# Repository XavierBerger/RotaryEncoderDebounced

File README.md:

# Rotary Encoder Debounced

A rotary encoder tracks shaft rotation by outputting pulses. However, mechanical switches in encoders suffer from contact bounce, causing false signals.

This projet propose a solution to debounced Rotary Encoder signal at hardware level.

## The Problem

When encoder contacts close or open, they bounce, creating multiple rapid signal changes. These can be misinterpreted as several rotations or direction changes.

*Signal captured on a rotary encoder without debouncer*

*Resulting signal of a noisy input*

## The solutions

### Software Debouncing is not statisfying

Software debouncing filters out noise but has drawbacks:

* Timing needs are precise and hard to maintain at varying speeds.

* Processing overhead increases, burdening limited systems.

* Complexity rises with advanced algorithms.

### Hardware Debouncing is more reliable

This project uses hardware to debounce signals reliably by associating low-pass filters with schmitt triggers.

#### Low-Pass Filter

A simple RC circuit smooths the signal by filtering high-frequency noise, averaging rapid changes.

Filter has been designed to have a cutoff frequency of 1,59kHz with a time constant of 100µs.

#### Schmitt Trigger

Schmitt trigger, with two voltage thresholds, converts the filtered signal to a clean digital output. Hysteresis prevents noise from causing false transitions.

This combination removes bounce issues and provide a clean signal where noise is removed.

Hardware has been designed to use the smallest possible PCB. Pin header have been placed to ensure connectivity as well as mounting solution. Pin header placement have been placed to be compatible with breadboards.

## Realisation
Schematic, PCB, 3D views are designed with KiCad 9 with the following plugins:

* Interactive Html Bom [🔗](https://github.com/openscopeproject/InteractiveHtmlBom)  
  See the bill of material [here](https://xavierberger.github.io/RotaryEncoderDebounced/ibom.html)
* KiCAD JLCPCB tools [🔗](https://github.com/bouni/kicad-jlcpcb-tools)  
  This plugin allows you to search the JLCPCB parts database, assign LCSC article numbers to your parts, generate production files for JLCPCB and much more.
* Fabrication Toolkit [🔗](https://github.com/bennymeg/Fabrication-Toolkit)  
  Toolkit for automating PCB fabrication process with KiCad and JLCPCB. 

*Note: I used* **Fabrication Toolkit** *to generate production file since I noticed that component orientation of component is correct while it wans't in* **KiCAD JLCPCB tools**.

Components have been choosen to be "**Basic**" parts of JLCPCB to reduce the manufactirung cost.

The cost of the PCB fabrication and SMD assembly (so without the rotary encoder and pin headers) is about 7€ for 5 pieces.

## Analysis of results

On the oscilloscope, we can see a clean signal. The noise has been filtered-out.

*Signal captured on a rotary encoder with hardware debouncer*

The resulting signal captured with a logical analyser is also clean.

*The resulting signal is clean*

Even when the capture rate is pushed up to the limit of the logical analyser, the signal remain clean.

Software debouncer is then no more needed and it is possible to base the algorithm on edge detection.

## License

Licensed under [CERN-OHL-P](LICENCE.txt). Free to use and modify.

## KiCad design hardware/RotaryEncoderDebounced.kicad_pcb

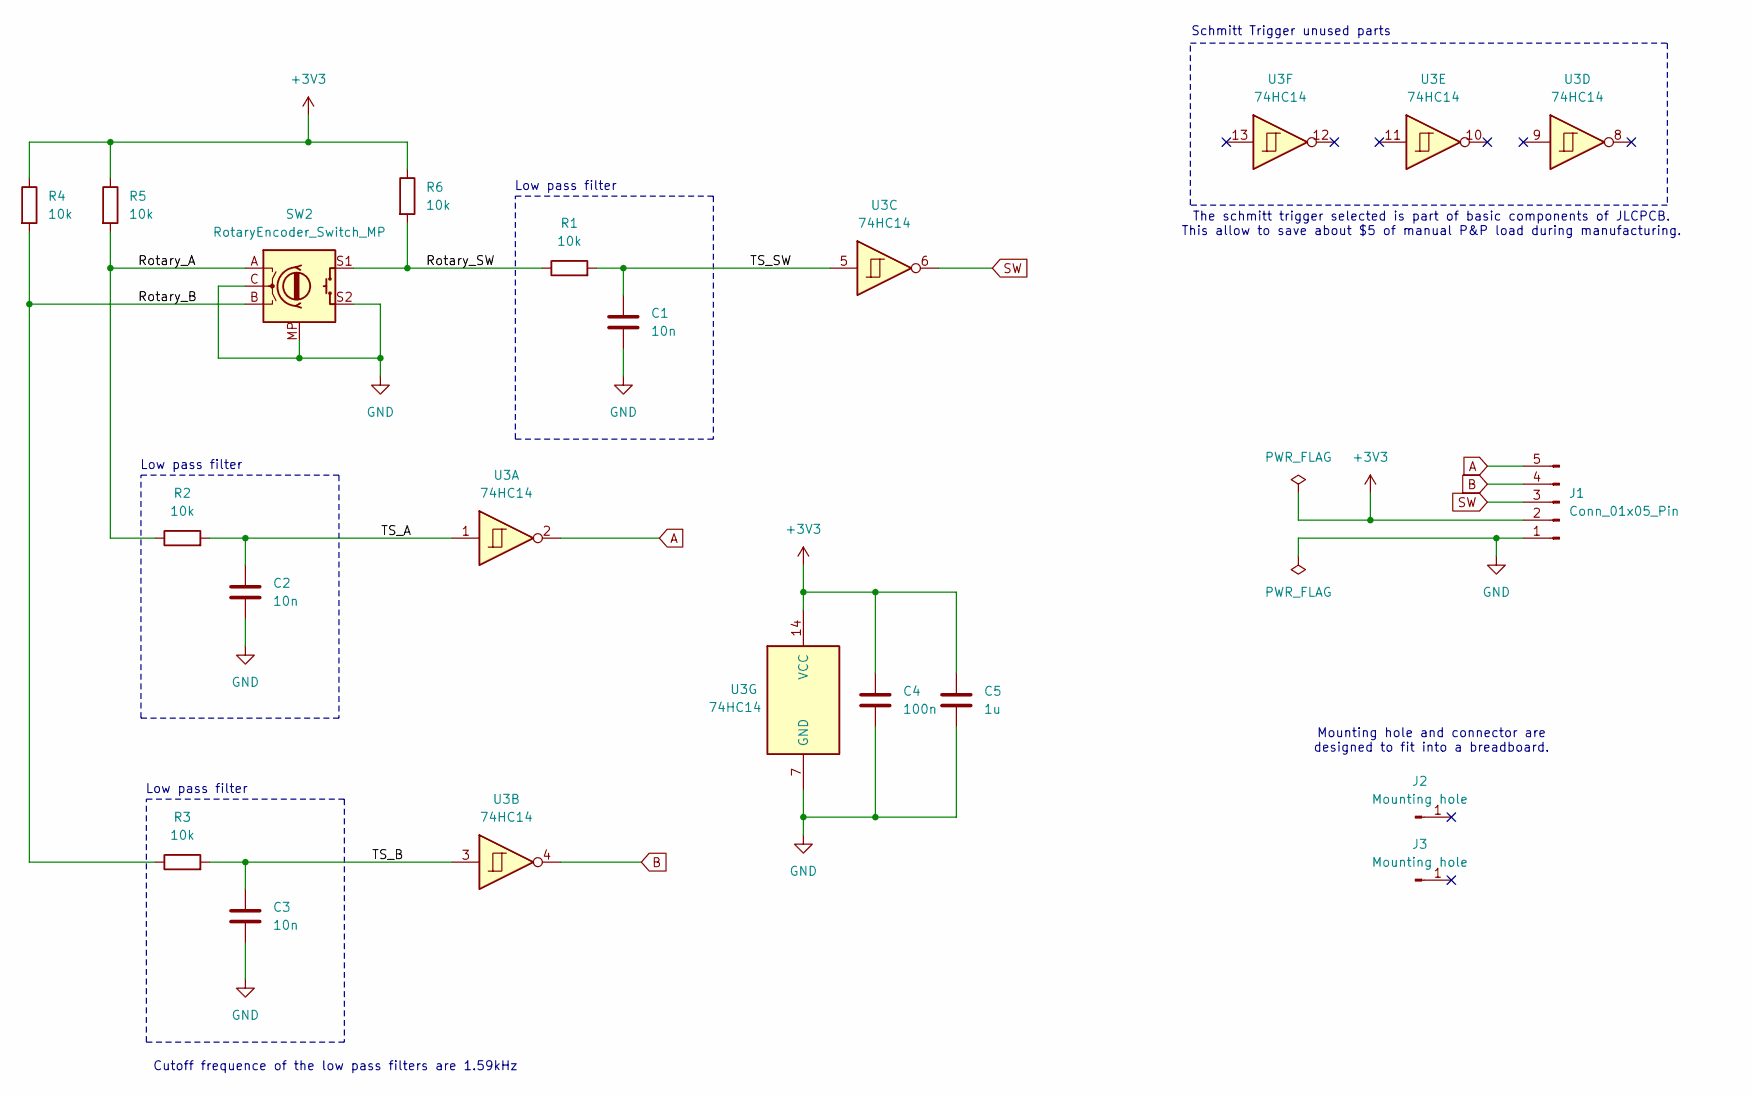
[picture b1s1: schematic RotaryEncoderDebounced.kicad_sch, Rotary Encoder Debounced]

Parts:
C1, C2, C3: 10n; C_0805_2012Metric
C4: 100n; C_0805_2012Metric
C5: 1u; C_0805_2012Metric
J1: Conn_01x05_Pin; PinHeader_1x05_P2.54mm_Vertical
J2, J3: Mounting hole; PinHeader_1x01_P2.54mm_Vertical
R1, R2, R3, R4, R5, R6: 10k; R_0805_2012Metric
SW2: RotaryEncoder_Switch_MP; RotaryEncoder_Alps_EC11E-Switch_Vertical_H20mm
U3: 74HC14; SOIC-14_3.9x8.7mm_P1.27mm

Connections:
+3V3: C4.1, C5.1, J1.2, R4.1, R5.1, R6.1, U3.14 (VCC)
/Rotary_A: R2.1, R5.2, SW2.A
/Rotary_B: R3.1, R4.2, SW2.B
/Rotary_SW: R1.1, R6.2, SW2.S1
/TS_A: C2.1, R2.2, U3.1
/TS_B: C3.1, R3.2, U3.3
/TS_SW: C1.1, R1.2, U3.5
A: J1.5, U3.2
B: J1.4, U3.4
GND: C1.2, C2.2, C3.2, C4.2, C5.2, J1.1, SW2.C, SW2.MP, SW2.S2, U3.7 (GND)
SW: J1.3, U3.6

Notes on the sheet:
Mounting hole and connector are designed to fit into a breadboard.
Low pass filter
Schmitt Trigger unused parts
Cutoff frequence of the low pass filters are 1.59kHz
The schmitt trigger selected is part of basic components of JLCPCB. This allow to save about $5 of manual P&P load during manufacturing.

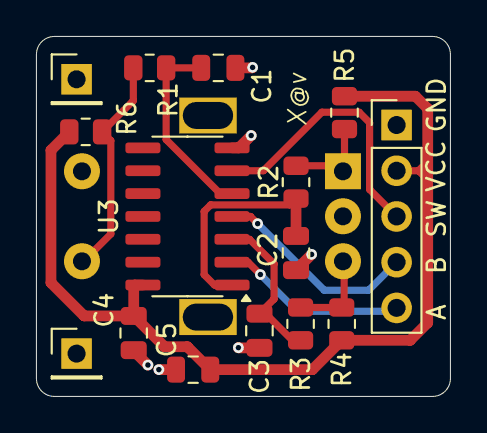
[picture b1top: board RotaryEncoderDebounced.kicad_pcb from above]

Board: 2 copper layers, 23.0 x 20.0 mm, 16 parts (1 on the bottom side), 11 nets.

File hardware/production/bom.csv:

Designator,Footprint,Quantity,Value,LCSC Part #
"C1, C2, C3",0805,3,10n,C1710
C4,0805,1,100n,C49678
C5,0805,1,1u,C28323
"R1, R2, R3, R4, R5, R6",0805,6,10k,C17414
U3,SOIC-14_3.9x8.7mm_P1.27mm,1,74HC14,C5605

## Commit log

2025-07-05 chore: Add License
2025-07-05 feat(hardware): Add KiCad design
2025-07-05 chore: Add .gitignore
2025-07-05 doc: Add datasheet of Schmitt Trigger and Rotary encoder
2025-07-05 doc: Update Readme and documentation
2025-07-05 doc: Update README to point to interactive bom in gh-pages
2025-07-05 doc: Fix typo in README
2025-07-11 doc: Update README (TLDR)
2025-07-11 doc: update 3D views
2025-07-18 doc: Add photo of PCB assembled

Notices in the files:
hardware/RotaryEncoderDebounced.kicad_pcb:
CERN-OHL-P 2025-07
hardware/RotaryEncoderDebounced.kicad_sch:
License : CERN-OHL-P
